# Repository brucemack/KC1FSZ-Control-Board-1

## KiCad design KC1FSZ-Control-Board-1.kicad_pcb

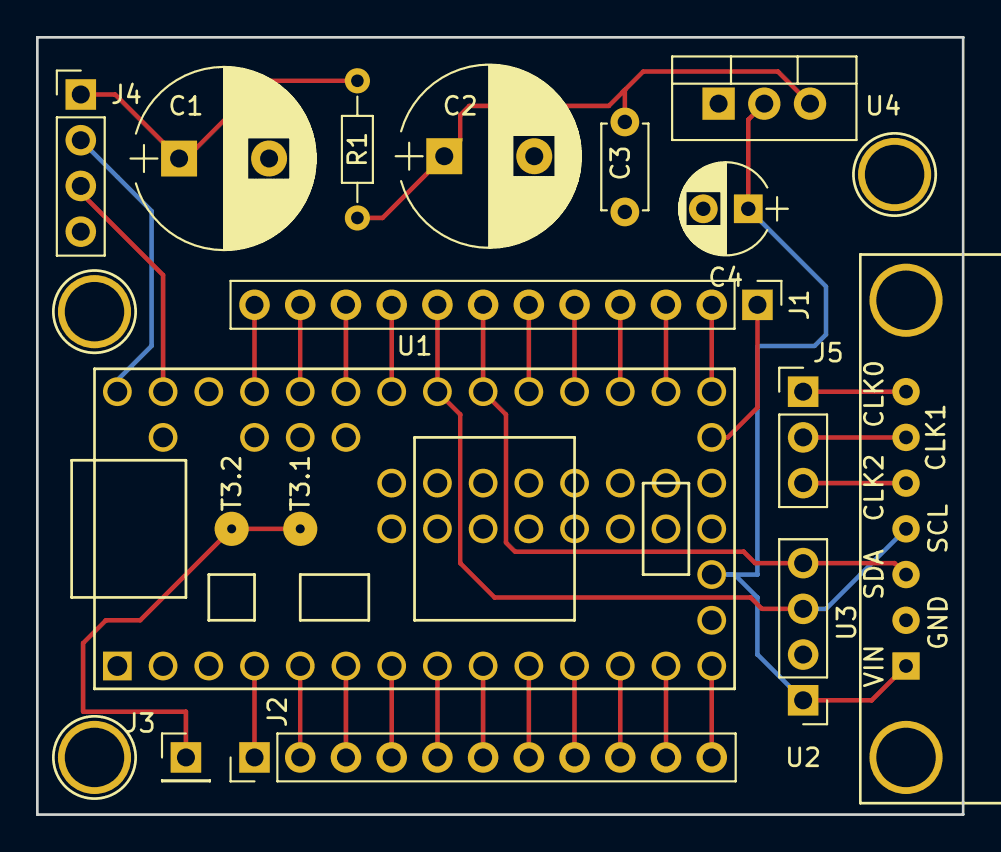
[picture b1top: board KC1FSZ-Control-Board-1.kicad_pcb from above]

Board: 2 copper layers, 51.4 x 43.2 mm, 14 parts (0 on the bottom side), 33 nets.

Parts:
C1, C2: 220u; CP_Radial_D10.0mm_P5.00mm
C3: 0.1u; C_Disc_D4.7mm_W2.5mm_P5.00mm
C4: 10u; CP_Radial_D5.0mm_P2.50mm
J1: Conn_01x12; Pin_Header_Straight_1x12_Pitch2.54mm
J2: Conn_01x11; Pin_Header_Straight_1x11_Pitch2.54mm
J3: Conn_01x01; Pin_Header_Straight_1x01_Pitch2.54mm
J4: Conn_01x04; Pin_Header_Straight_1x04_Pitch2.54mm
J5: Conn_01x03; Pin_Header_Straight_1x03_Pitch2.54mm
R1: 10; R_Axial_DIN0204_L3.6mm_D1.6mm_P7.62mm_Horizontal
U1: Teensy3.2; Teensy30_31_32_LC
U2: OLED_128x64; Pin_Header_Straight_1x04_Pitch2.54mm
U3: Adafruit_SI5351a; Adafruit_SI5351a_Module
U4: LM1117-3.3; TO-220_Vertical

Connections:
AUX_CLK: J5.2, U3.6
BFO_CLK: J5.3, U3.5
GND: C1.2, C2.2, C3.2, C4.2, J4.4, U1.1, U2.2, U3.2, U4.1
I2C_SCL: J1.8, U1.26, U2.3, U3.4
I2C_SDA: J1.7, U1.25, U2.4, U3.3
unnamed: C2.1, C3.1, R1.1, U4.3
unnamed: J1.1, U1.19
unnamed: J1.2, U1.20
unnamed: J1.3, U1.21
unnamed: J1.4, U1.22
unnamed: J1.5, U1.23
unnamed: J1.6, U1.24
unnamed: J1.9, U1.27
unnamed: J1.10, U1.28
unnamed: J1.11, U1.29
unnamed: J1.12, U1.30
unnamed: J2.1, U1.4
unnamed: J2.2, U1.5
unnamed: J2.3, U1.6
unnamed: J2.4, U1.7
unnamed: J2.5, U1.8
unnamed: J2.6, U1.9
unnamed: J2.7, U1.10
unnamed: J2.8, U1.11
unnamed: J2.9, U1.12
unnamed: J2.10, U1.13
unnamed: J2.11, U1.14
unnamed: J3.1, U1.52
unnamed: J4.2, U1.33
unnamed: J4.3, U1.32
V33: C4.1, U1.16, U2.1, U3.1, U4.2
VFO_CLK: J5.1, U3.7
VIN: C1.1, J4.1, R1.2
